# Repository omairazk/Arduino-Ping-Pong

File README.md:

# Arduino Ping Pong (Puck Game)

Two-player reaction-based electronic puck game built using Arduino Nano.

## Features
- Joystick-controlled gameplay
- Real-time score tracking with 7-segment displays
- Shift-register-based display control
- Audio feedback via buzzer
- Custom-designed PCB

## Repository Structure
- Software/ – Arduino source code
- PONG/ – Schematics, PCB layouts
- PONG_GERB/ - Drill, Gerber Files
- Datasheets/ - Parts used

## PCB Build & Assembly Instructions

This repository contains all files required to manufacture, assemble, and program the Arduino Ping Pong PCB.

### 1. PCB Manufacturing
Fabricate the PCB using the Gerber and drill files located in:
- `PONG/`
- `PONG_GERB/`

Upload these files to a standard PCB manufacturer (e.g., JLCPCB, PCBWay) using typical default settings:
- Board thickness: 1.6 mm
- Copper weight: 1 oz
- Surface finish: HASL or ENIG
- Solder mask: Any color

### 2. Required Components
- Arduino Nano
- 74HC595 shift registers
- Two joystick modules
- Two 7-segment displays
- tow Buzzer
- 330ohm Resistors (current-limiting and pull-ups as specified in schematic)
- 1 uf Capacitors (decoupling)
- Female connectors, normal and 90 degree configuration
- Solder station

### 3. Required Softwareew
- Arduino ide
- Kicad

Refer to the schematic for exact component values and connections:
- `PONG/`

### 4. PCB Assembly
1. Begin by soldering low-profile components (resistors and capacitors).
2. Solder ICs (74HC595 shift registers) and header pins.
3. Mount and solder the Arduino Nano.
4. Install the 7-segment displays, joystick connectors, and buzzer.
5. Visually inspect all solder joints for shorts, cold joints, or misalignment.

### 5. Firmware Upload
1. Connect the Arduino Nano to a computer via USB.
2. Open the Arduino IDE.
3. Load the firmware located in:
   - `Software/`
4. Select the correct board (Arduino Nano) and COM port.
5. Upload the firmware to the board.

### 6. Initial Power-On and Testing
- Power the board using USB (5 V).
- Confirm that the 7-segment displays initialize correctly.
- Verify joystick inputs respond to movement.
- Check that the buzzer activates during scoring events.

### 7. Gameplay Verification
- Ensure both players can control their Joysticks.
- Confirm scores increment correctly.
- Verify game reset and restart behavior.

Once all checks pass, the PCB is ready for normal gameplay, HAVE FUN!!

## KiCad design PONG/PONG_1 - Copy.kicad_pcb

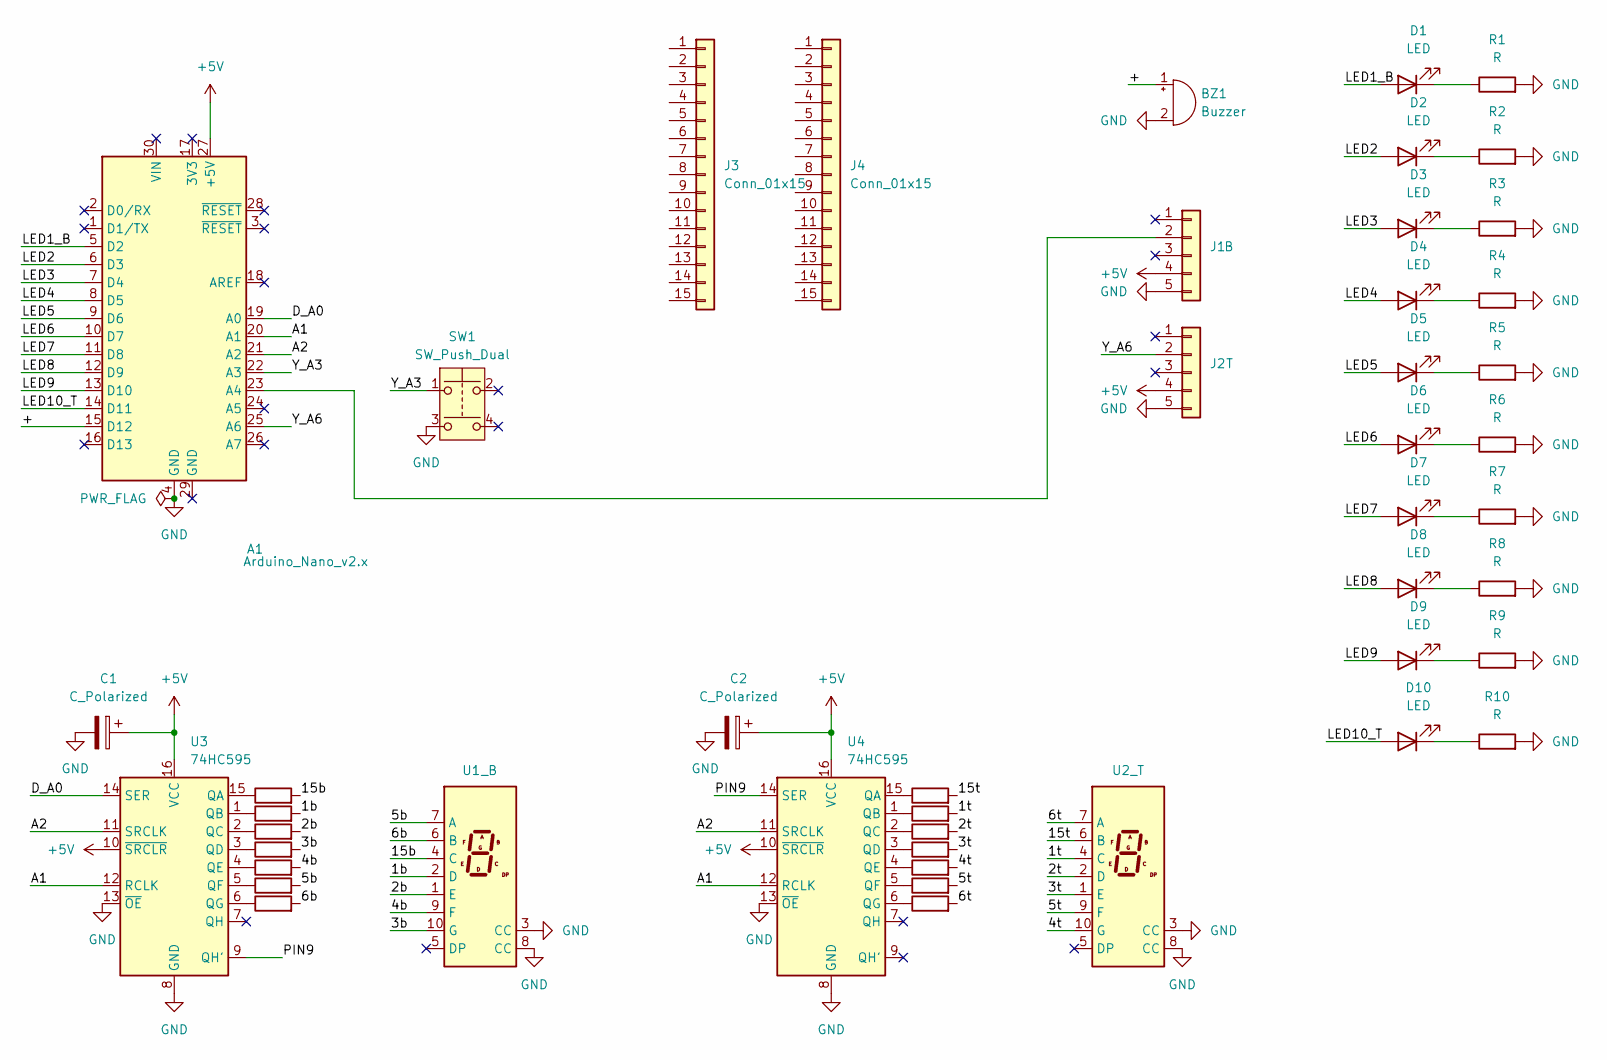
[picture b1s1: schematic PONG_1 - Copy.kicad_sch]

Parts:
A1: Arduino_Nano_v2.x; Arduino_Nano
BZ1: Buzzer; Buzzer_TDK_PS1240P02BT_D12.2mm_H6.5mm
C1, C2: C_Polarized; CP_Radial_D5.0mm_P2.50mm
D1, D2, D3, D4, D5, D6, D7, D8, D9, D10: LED; LED_D5.0mm
J1: B; PinSocket_1x05_P2.54mm_Horizontal
J2: T; PinSocket_1x05_P2.54mm_Horizontal
J3, J4: Conn_01x15; PinSocket_1x15_P2.54mm_Vertical
R1, R2, R3, R4, R5, R6, R7, R8, R9, R10, R11, R12, R13, R14, R15, R16, R17, R18, R19, R20, R21, R22, R23, R24: R; R_Axial_DIN0207_L6.3mm_D2.5mm_P7.62mm_Horizontal
SW1: SW_Push_Dual; SW_Push_2P1T_Toggle_CK_PVA1xxH1xxxxxxV2
U1: _B; D1X8K
U2: _T; D1X8K
U3, U4: 74HC595; DIP-16_W7.62mm

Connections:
+5V: A1.27 (+5V), C1.1, C2.1, J1.4, J2.4, U3.10 (~SRCLR), U3.16 (VCC), U4.10 (~SRCLR), U4.16 (VCC)
/1b: R12.2, U1.2 (D)
/1t: R19.2, U2.4 (C)
/2b: R13.2, U1.1 (E)
/2t: R20.2, U2.2 (D)
/3b: R14.2, U1.10 (G)
/3t: R21.2, U2.1 (E)
/4b: R15.2, U1.9 (F)
/4t: R22.2, U2.10 (G)
/5b: R16.2, U1.7 (A)
/5t: R23.2, U2.9 (F)
/6b: R17.2, U1.6 (B)
/6t: R24.2, U2.7 (A)
/15b: R11.2, U1.4 (C)
/15t: R18.2, U2.6 (B)
/+: A1.15 (D12), BZ1.1 (+)
/A1: A1.20 (A1), U3.12 (RCLK), U4.12 (RCLK)
/A2: A1.21 (A2), U3.11 (SRCLK), U4.11 (SRCLK)
/D_A0: A1.19 (A0), U3.14 (SER)
/LED1_B: A1.5 (D2), D1.2 (A)
/LED2: A1.6 (D3), D2.2 (A)
/LED3: A1.7 (D4), D3.2 (A)
/LED4: A1.8 (D5), D4.2 (A)
/LED5: A1.9 (D6), D5.2 (A)
/LED6: A1.10 (D7), D6.2 (A)
/LED7: A1.11 (D8), D7.2 (A)
/LED8: A1.12 (D9), D8.2 (A)
/LED9: A1.13 (D10), D9.2 (A)
/LED10_T: A1.14 (D11), D10.2 (A)
/PIN9: U3.9 (QH'), U4.14 (SER)
/Y_A3: A1.22 (A3), SW1.1
/Y_A6: A1.25 (A6), J2.2
GND: A1.4 (GND), BZ1.2 (-), C1.2, C2.2, J1.5, J2.5, R1.2, R2.2, R3.2, R4.2, R5.2, R6.2, R7.2, R8.2, R9.2, R10.2, SW1.3, U1.3 (CC), U1.8 (CC), U2.3 (CC), U2.8 (CC), U3.8 (GND), U3.13 (~OE), U4.8 (GND), U4.13 (~OE)
unnamed: A1.23 (A4), J1.2
unnamed: D1.1 (K), R1.1
unnamed: D2.1 (K), R2.1
unnamed: D3.1 (K), R3.1
unnamed: D4.1 (K), R4.1
unnamed: D5.1 (K), R5.1
unnamed: D6.1 (K), R6.1
unnamed: D7.1 (K), R7.1
unnamed: D8.1 (K), R8.1
unnamed: D9.1 (K), R9.1
unnamed: D10.1 (K), R10.1
unnamed: R11.1, U3.15 (QA)
unnamed: R12.1, U3.1 (QB)
unnamed: R13.1, U3.2 (QC)
unnamed: R14.1, U3.3 (QD)
unnamed: R15.1, U3.4 (QE)
unnamed: R16.1, U3.5 (QF)
unnamed: R17.1, U3.6 (QG)
unnamed: R18.1, U4.15 (QA)
unnamed: R19.1, U4.1 (QB)
unnamed: R20.1, U4.2 (QC)
unnamed: R21.1, U4.3 (QD)
unnamed: R22.1, U4.4 (QE)
unnamed: R23.1, U4.5 (QF)
unnamed: R24.1, U4.6 (QG)

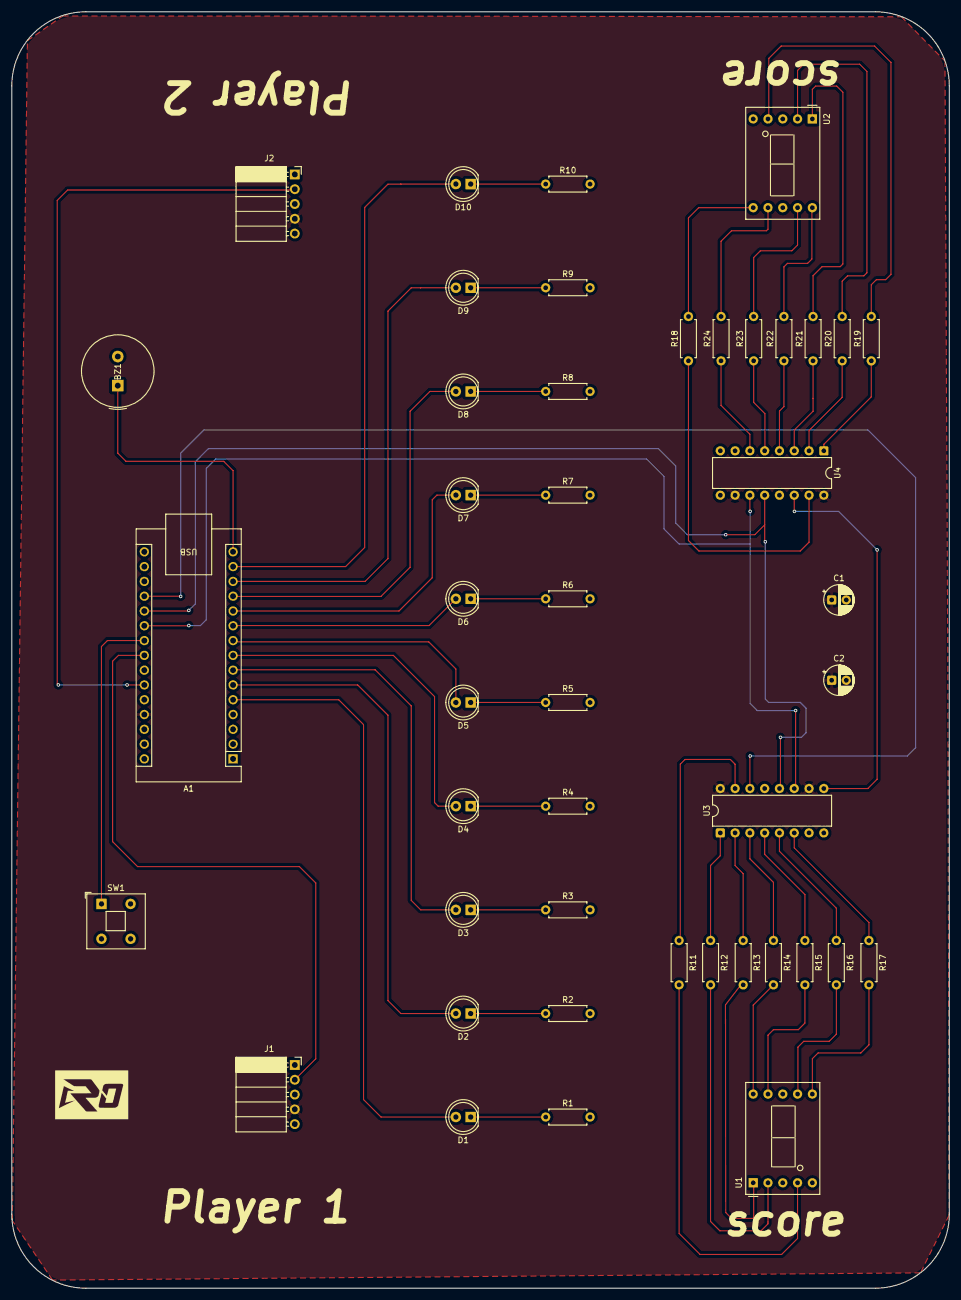
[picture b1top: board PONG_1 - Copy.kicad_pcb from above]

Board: 2 copper layers, 161.0 x 219.2 mm, 45 parts (0 on the bottom side), 58 nets.
